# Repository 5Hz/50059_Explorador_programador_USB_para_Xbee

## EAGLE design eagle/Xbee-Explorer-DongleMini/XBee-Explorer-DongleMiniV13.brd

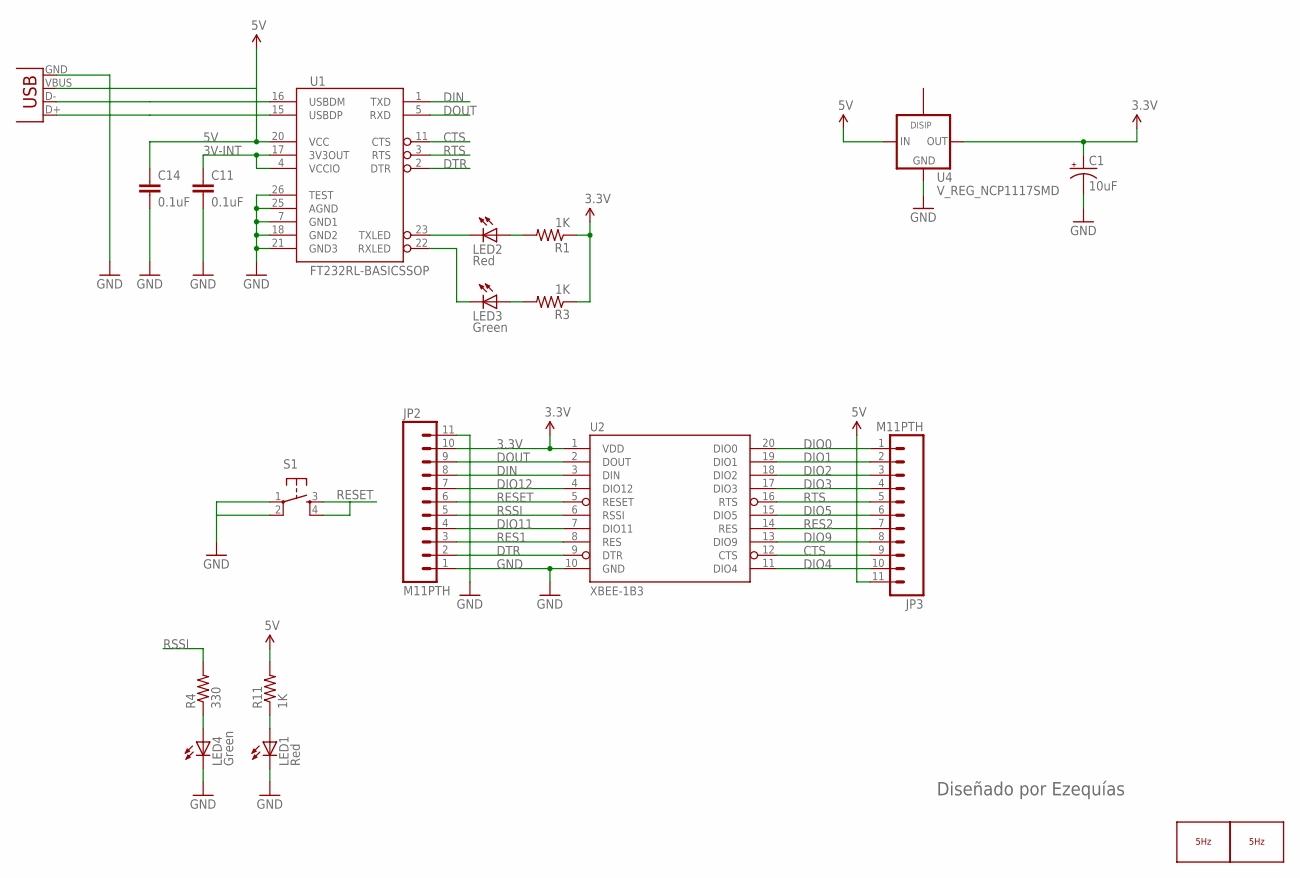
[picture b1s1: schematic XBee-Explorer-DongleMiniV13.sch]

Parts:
C1: 10uF; EIA3216
C11, C14: 0.1uF; 0402-CAP
JP2, JP3: M11PTH; 1X11
LED1, LED2: Red; LED-0603
LED3, LED4: Green; LED-0603
LOGO1: LOGO_5HZ_MAIN_10MM; 5HZ_LOGO_MAIN_10MM
LOGO2: LOGO_5HZ_H_10MM; 5HZ_LOGO_H_10MM
R1, R3, R11: 1K; 0603-RES
R4: 330; 0603-RES
S1: TAC_SWITCHSMD; TACTILE_SWITCH_SMD
U1: FT232RL-BASICSSOP; SSOP28DB
U2: XBEE-1B3; XBEE-SMD
U4: V_REG_NCP1117SMD; SOT223
X1: USBSMD; USB-MINIB

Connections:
3.3V: C1.A (+), JP2.10, R1.1, R3.1, U2.1 (VDD), U4.2 (OUT)
3V-INT: C11.1, U1.4 (VCCIO), U1.17 (3V3OUT)
5V: C14.1, JP3.11, R11.2, U1.20 (VCC), U4.3 (IN), X1.VBUS
CTS: JP3.9, U1.11 (CTS), U2.12 (CTS)
DIN: JP2.8, U1.1 (TXD), U2.3 (DIN)
DIO0: JP3.1, U2.20 (DIO0)
DIO1: JP3.2, U2.19 (DIO1)
DIO2: JP3.3, U2.18 (DIO2)
DIO3: JP3.4, U2.17 (DIO3)
DIO4: JP3.10, U2.11 (DIO4)
DIO5: JP3.6, U2.15 (DIO5)
DIO9: JP3.8, U2.13 (DIO9)
DIO11: JP2.4, U2.7 (DIO11)
DIO12: JP2.7, U2.4 (DIO12)
DOUT: JP2.9, U1.5 (RXD), U2.2 (DOUT)
DTR: JP2.2, U1.2 (DTR), U2.9 (DTR)
GND: C1.C (-), C11.2, C14.2, JP2.1, JP2.11, LED1.C, LED4.C, S1.1, S1.2, U1.7 (GND1), U1.18 (GND2), U1.21 (GND3), U1.25 (AGND), U1.26 (TEST), U2.10 (GND), U4.1 (GND), X1.GND
unnamed: LED2.A, R1.2
unnamed: LED4.A, R4.1
unnamed: U1.16 (USBDM), X1.D-
unnamed: LED3.A, R3.2
unnamed: U1.15 (USBDP), X1.D+
unnamed: LED1.A, R11.1
RES1: JP2.3, U2.8 (RES)
RES2: JP3.7, U2.14 (RES)
RESET: JP2.6, S1.3, S1.4, U2.5 (RESET)
RSSI: JP2.5, R4.2, U2.6 (RSSI)
RTS: JP3.5, U1.3 (RTS), U2.16 (RTS)
RXLED: LED3.C, U1.22 (RXLED)
TXLED: LED2.C, U1.23 (TXLED)

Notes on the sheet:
Diseñado por Ezequías

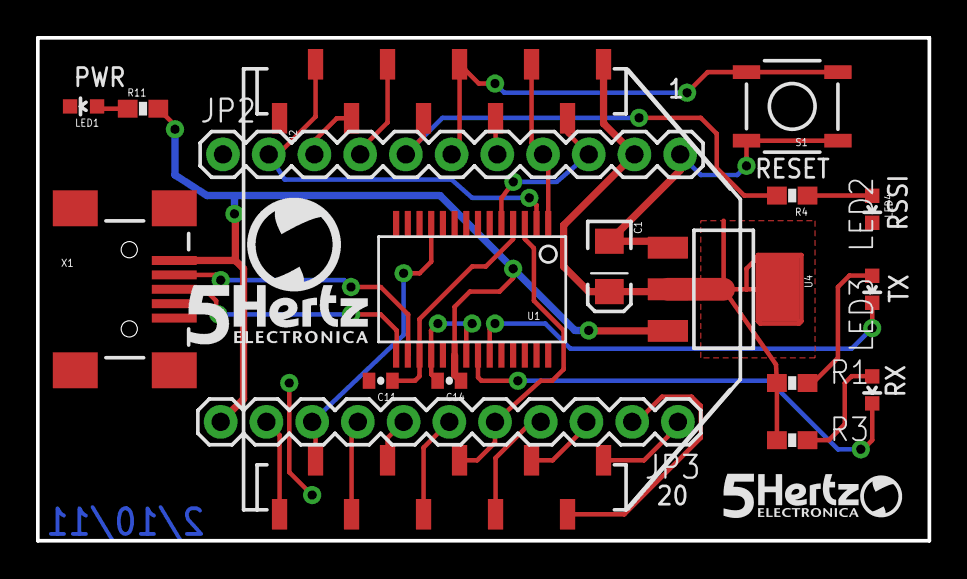
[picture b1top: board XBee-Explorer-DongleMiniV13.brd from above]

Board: 2 copper layers, 49.5 x 27.9 mm, 20 parts (0 on the bottom side), 30 nets.

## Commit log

2014-01-13 creación
